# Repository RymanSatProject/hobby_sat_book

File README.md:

# #趣味で作る人工衛星

本リポジトリは、[オーム社 #趣味で作る人工衛星](https://www.ohmsha.co.jp/book/9784274230387/)のサポートページです。

## 構成

### [00_errata](00_errata)

書籍の正誤表が入っています。

### [01_CDH_OBC](01_CDH_OBC)

第7章C&DH系OBCソフトウェアのソースコード

### [02_Mission_OBC](02_Mission_OBC)

第7章ミッションOBCソフトウェアのソースコードおよびセットアップスクリプトが入っています。

### [03_Telecom_OBC](03_Telecom_OBC)

第7章通信OBCソフトウェアのソースコードが入っています。

### [04_Ground_Sta](04_Ground_Sta)

第7章地上局ソフトウェアのインストーラが入っています。

### [05_Schematic](05_Schematic)

第7章EM基板のKiCadファイルが入っています。回路図とCAD画像も入れてあるので、基板作成時にご参照ください。

### [10_Ch7_Sup](10_Ch7_Sup)

第7章の各種補足説明が入っています。

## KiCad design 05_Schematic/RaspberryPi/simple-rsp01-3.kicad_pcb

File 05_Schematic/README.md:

# 回路図面

書籍で作成する基板の回路図を保存しています。使用ソフトウエアはKiCAD (https://www.kicad.org/download/) です。Version6.0以降であれば問題ないと思います。
基板制作時の部品配置や配線の参考にご利用ください。

RaspberryPi RaspberryPiの搭載されている下部基板の図面です。

esp32 Esp32の搭載されている背面基板の図面です。

stm32 STM32の搭載されている上部基板の図面です。

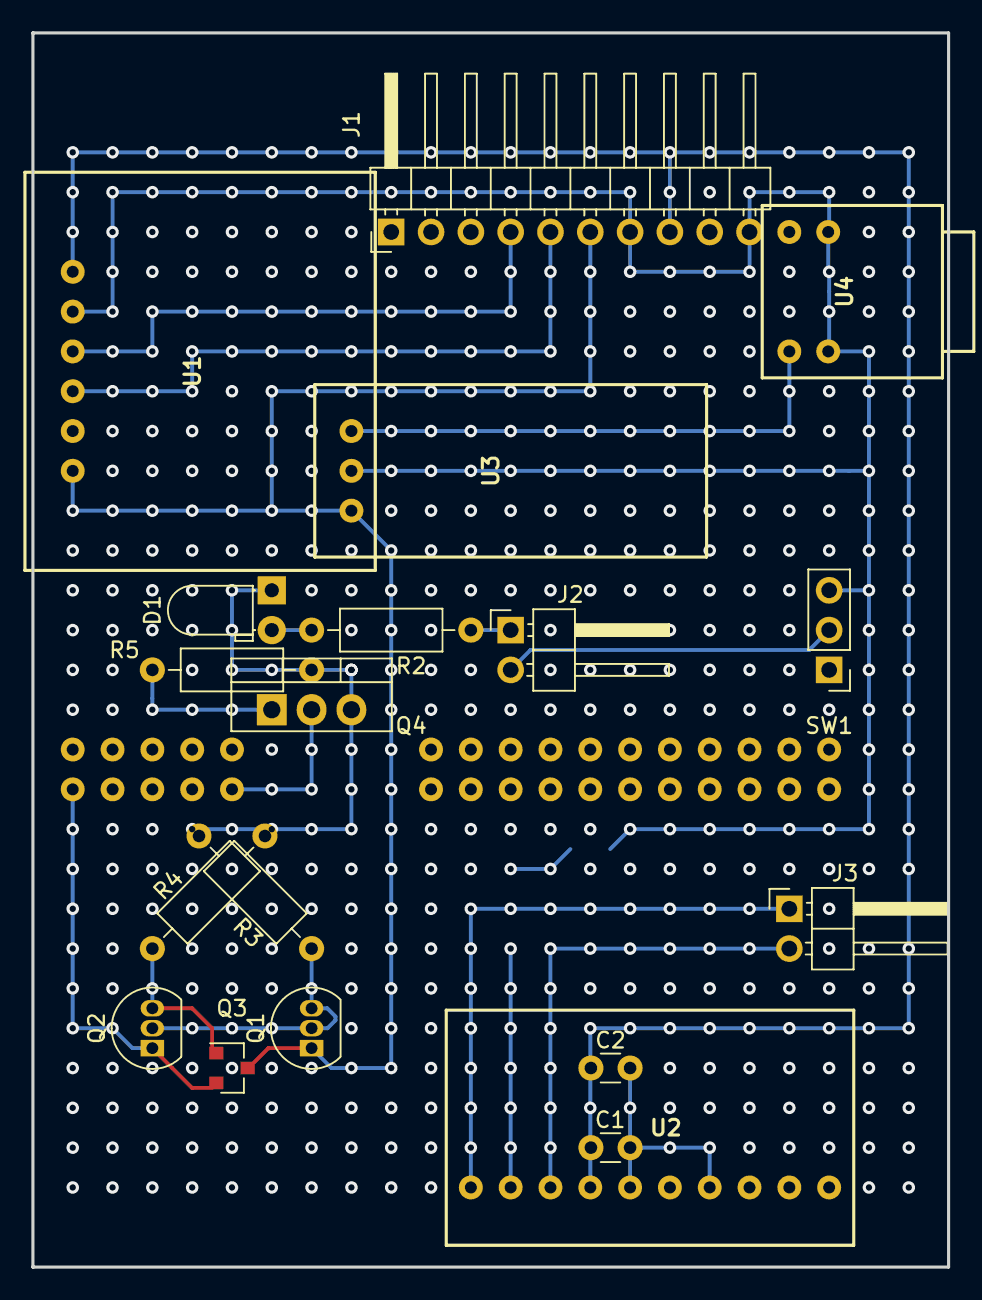
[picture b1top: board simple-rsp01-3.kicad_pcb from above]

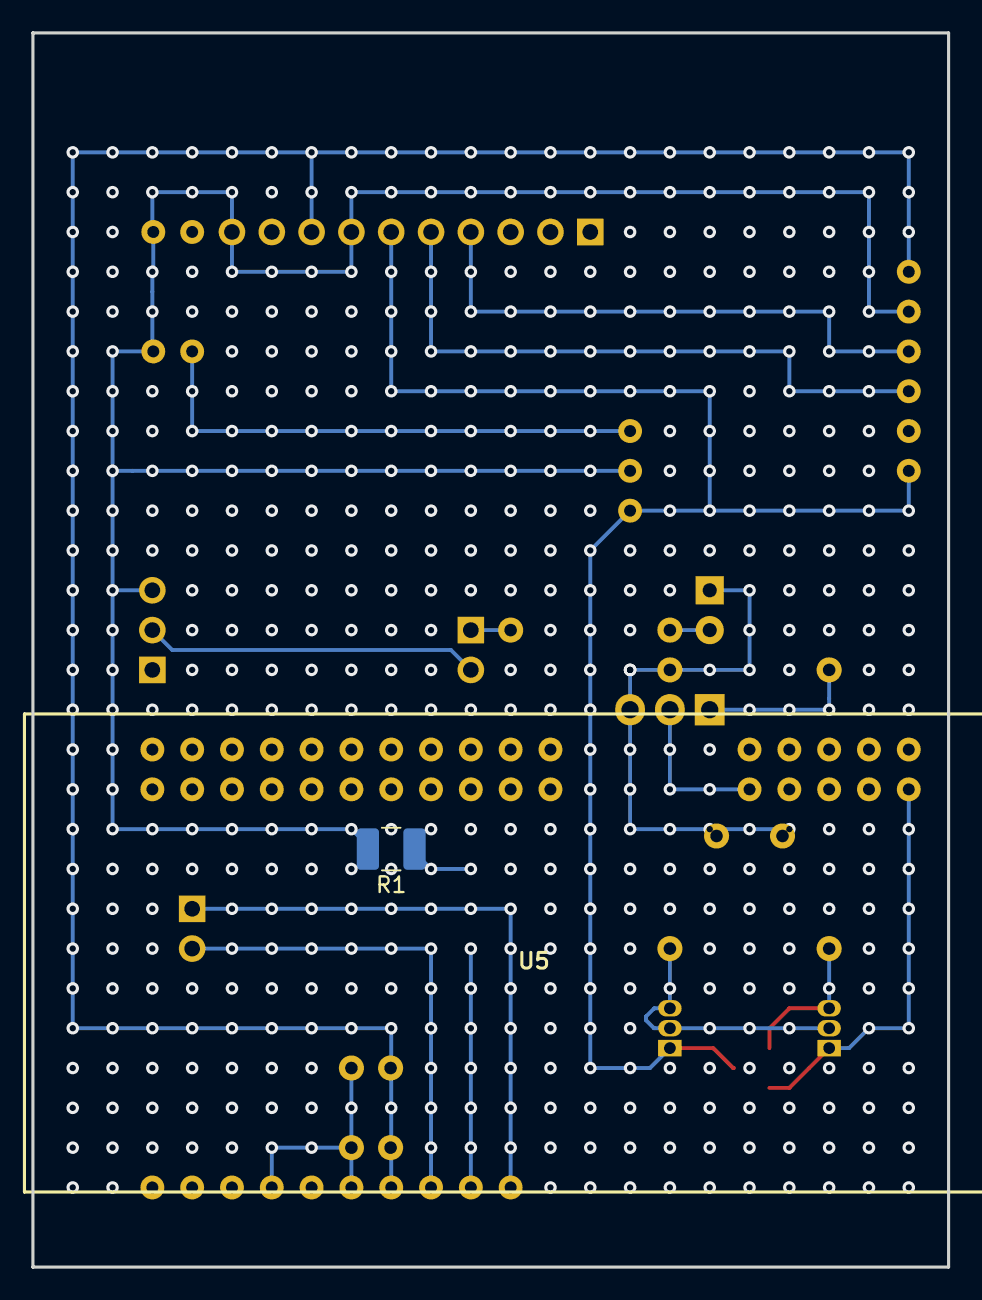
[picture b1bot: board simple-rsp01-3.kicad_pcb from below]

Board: 2 copper layers, 58.4 x 78.7 mm, 21 parts (2 on the bottom side), 19 nets.

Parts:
C1: 0.1uF; C_Disc_D3.0mm_W1.6mm_P2.50mm
C2: 10uF; C_Disc_D3.0mm_W1.6mm_P2.50mm
D1: LED; LED_D3.0mm_Horizontal_O1.27mm_Z2.0mm
J1: Conn_01x10; PinHeader_1x10_P2.54mm_Horizontal
J2, J3: Conn_01x02; PinHeader_1x02_P2.54mm_Horizontal
Q1, Q2: 2N5401L-B-T92-K; TO-92_Inline
Q3: DMG3415U; SOT-23
Q4: MTB30N06I3; TO-220-3_Vertical
R1: 0.24; R_1210_3225Metric_Pad1.42x2.65mm_HandSolder
R2: 330; R_Axial_DIN0207_L6.3mm_D2.5mm_P10.16mm_Horizontal
R3, R4, R5: 10k; R_Axial_DIN0207_L6.3mm_D2.5mm_P10.16mm_Horizontal
SW1: SW_SPDT; PinHeader_1x03_P2.54mm_Vertical
U1: INA219
U2: DRV8830
U3: LXDC55
U4: USBconnector
U5: Raspi; Raspy

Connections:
+3V3: C1.1, C2.1, J1.8, U1.1, U2.4
+4V: J1.6, Q1.1, Q3.3, U1.6, U3.3
+5V: U3.1, U4.1
BAT+: J2.1, R2.1, U1.5
BAT-: J2.2, SW1.2
FROM_Raspi_TX: J1.1, U5.3
GND: C1.2, C2.2, D1.1, J1.7, J1.10, Q4.3, R1.2, R3.2, R4.2, R5.1, SW1.3, U1.2, U2.5, U2.7, U3.2, U4.2, U4.3
MOTOR1: J3.1, U2.1
MOTOR2: J3.2, U2.3
unnamed: D1.2, R2.2
unnamed: Q1.2, Q1.3, Q2.2, R3.1
unnamed: Q2.3, Q3.1, R4.1
unnamed: Q4.2, U5.2
unnamed: R1.1, U2.2
Raspy_3.3V: Q2.1, Q3.2, U5.1
Raspy_Pwrctl: J1.3, Q4.1, R5.2
SCL: J1.4, U1.3, U2.10
SDA: J1.5, U1.4, U2.9
TO_Raspi_RXD: J1.2, U5.4

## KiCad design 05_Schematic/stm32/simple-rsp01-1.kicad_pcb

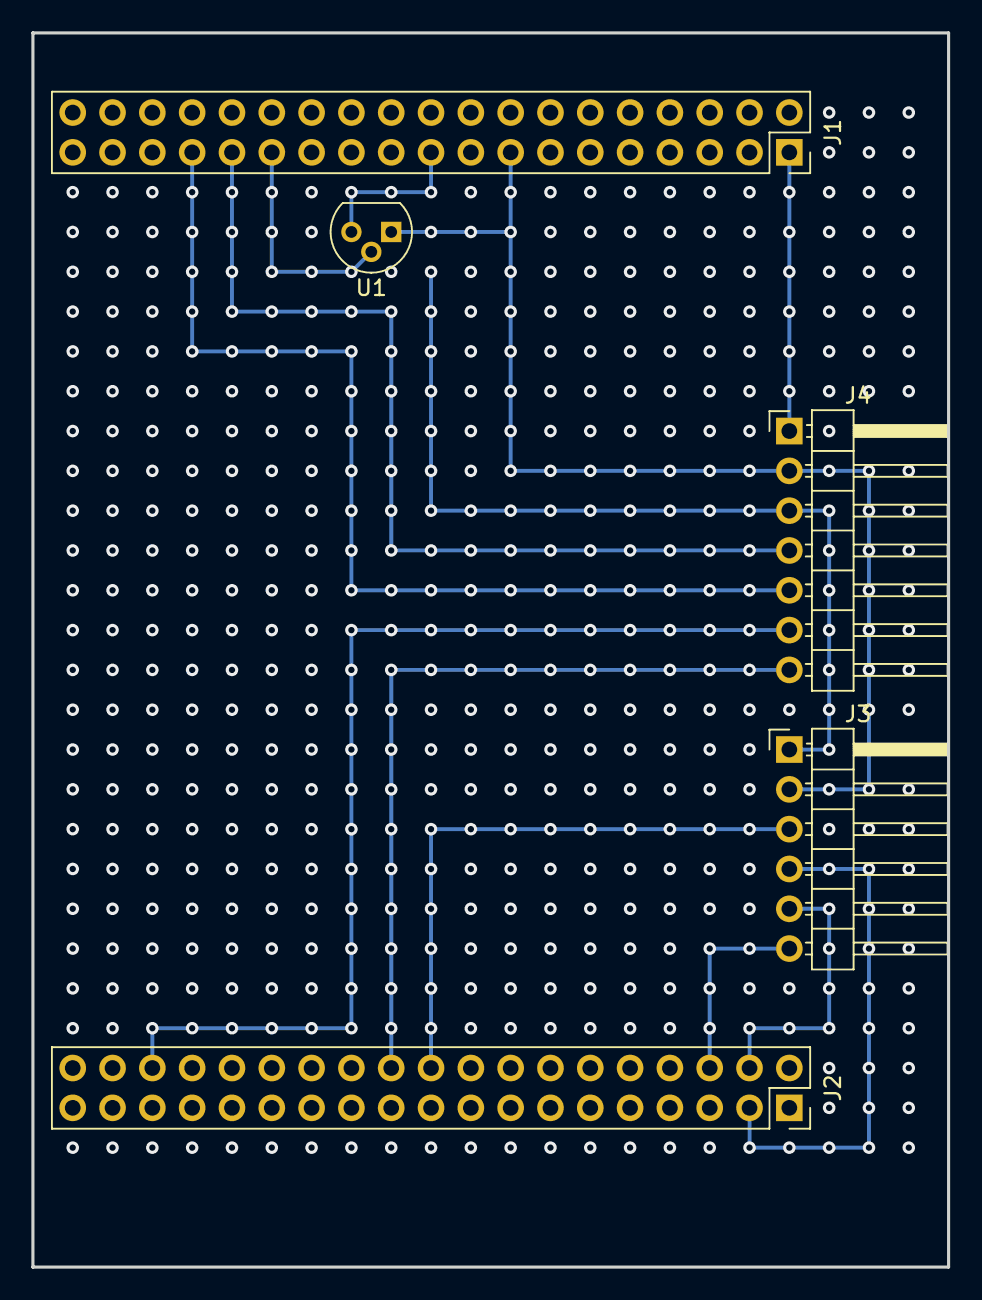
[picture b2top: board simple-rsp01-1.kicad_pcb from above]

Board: 2 copper layers, 58.4 x 78.7 mm, 5 parts (0 on the bottom side), 12 nets.

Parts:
J1, J2: Conn_02x19_Odd_Even; PinSocket_2x19_P2.54mm_Vertical
J3: Conn_01x06; PinHeader_1x06_P2.54mm_Horizontal
J4: Conn_01x07; PinHeader_1x07_P2.54mm_Horizontal
U1: LM61; TO-92

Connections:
+3V3: J1.16, J3.2, J4.2, U1.1
ESP32_GPIO: J1.2, J4.1
FROM_ESP32_TXD: J2.20, J3.3
FROM_Raspi_TX: J2.34, J4.6
GND: J1.20, J3.1, J4.3, U1.3
unnamed: J1.28, U1.2
Raspy_Pwrctl: J1.32, J4.5
SCL: J2.4, J3.5
SDA: J2.6, J3.6
SLIDE_VOL: J1.30, J4.4
TO_ESP32_RXD: J2.3, J3.4
TO_Raspi_RXD: J2.22, J4.7

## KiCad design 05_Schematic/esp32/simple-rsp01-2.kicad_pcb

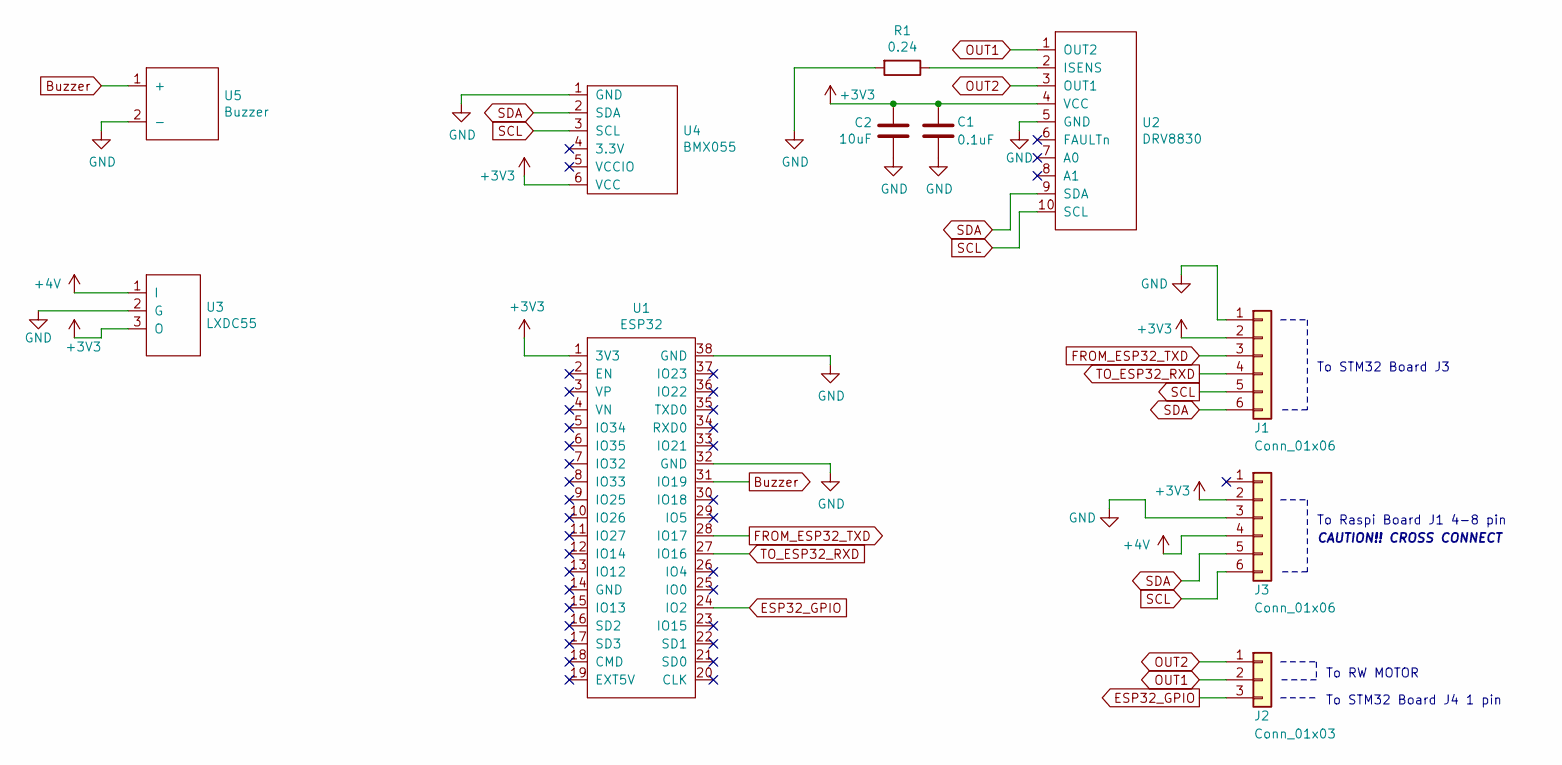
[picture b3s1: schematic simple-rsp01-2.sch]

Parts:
C1: 0.1uF; C_Disc_D3.0mm_W1.6mm_P2.50mm
C2: 10uF; C_Disc_D3.0mm_W1.6mm_P2.50mm
J1, J3: Conn_01x06; PinHeader_1x06_P2.54mm_Horizontal
J2: Conn_01x03; PinHeader_1x03_P2.54mm_Horizontal
R1: 0.24; R_1210_3225Metric_Pad1.42x2.65mm_HandSolder
U1: ESP32
U2: DRV8830
U3: LXDC55
U4: BMX055
U5: Buzzer

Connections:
+3V3: C1.1, C2.1, J1.2, J3.2, U1.1 (3V3), U2.4 (VCC), U3.3 (O), U4.6 (VCC)
+4V: J3.4, U3.1 (I)
Buzzer: U1.31 (IO19), U5.1 (+)
ESP32_GPIO: J2.3, U1.24 (IO2)
FROM_ESP32_TXD: J1.3, U1.28 (IO17)
GND: C1.2, C2.2, J1.1, J3.3, R1.2, U1.32 (GND), U1.38 (GND), U2.5 (GND), U3.2 (G), U4.1 (GND), U5.2 (-)
unnamed: R1.1, U2.2 (ISENS)
OUT1: J2.2, U2.1 (OUT2)
OUT2: J2.1, U2.3 (OUT1)
SCL: J1.5, J3.6, U2.10 (SCL), U4.3 (SCL)
SDA: J1.6, J3.5, U2.9 (SDA), U4.2 (SDA)
TO_ESP32_RXD: J1.4, U1.27 (IO16)

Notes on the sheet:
To STM32 Board J3
To RW MOTOR
To STM32 Board J4 1 pin
To Raspi Board J1 4-8 pin
CAUTION!! CROSS CONNECT

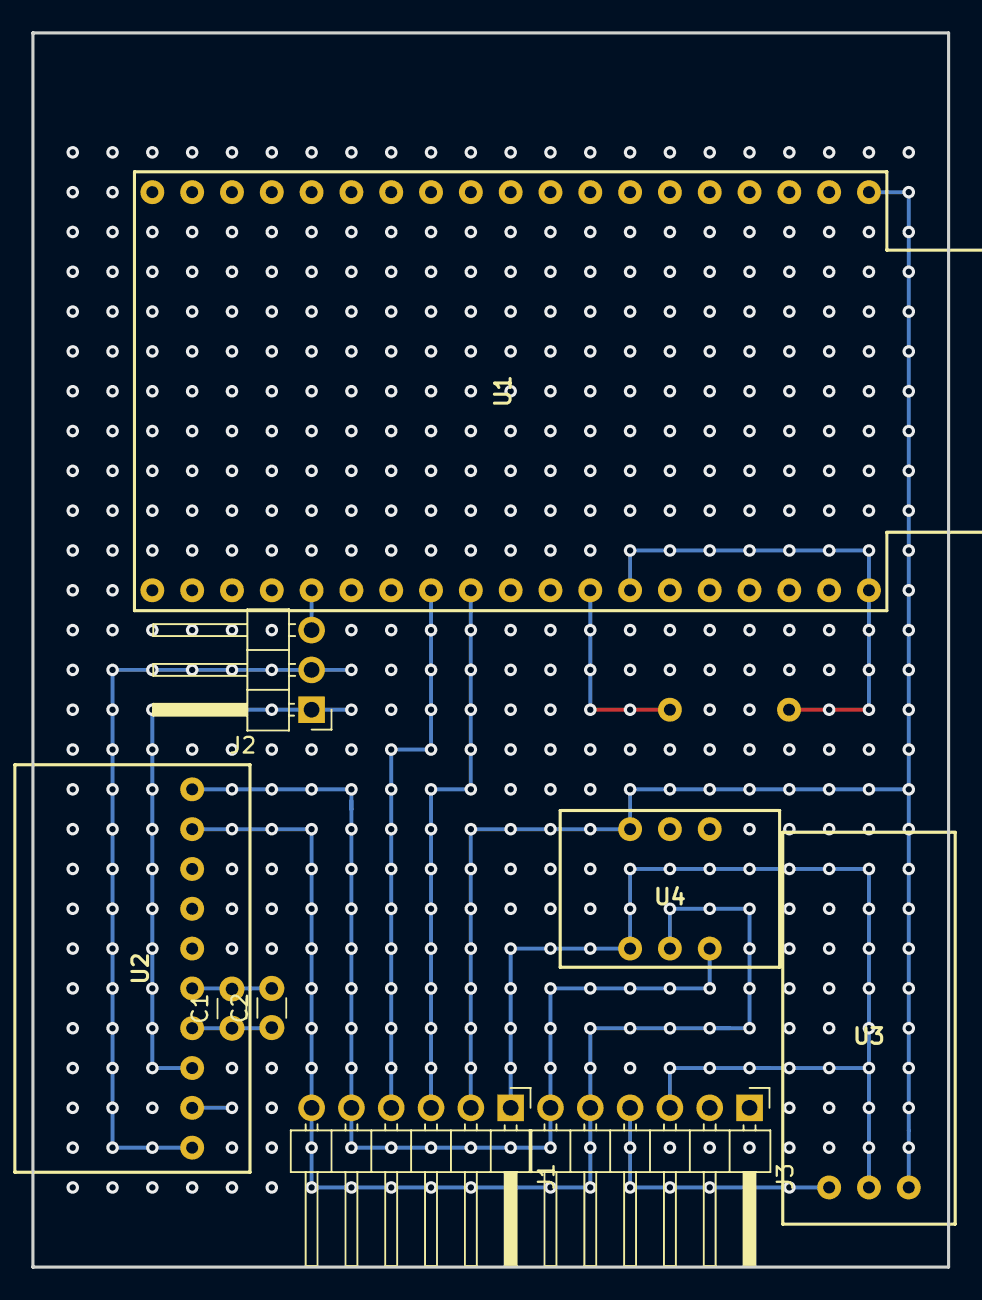
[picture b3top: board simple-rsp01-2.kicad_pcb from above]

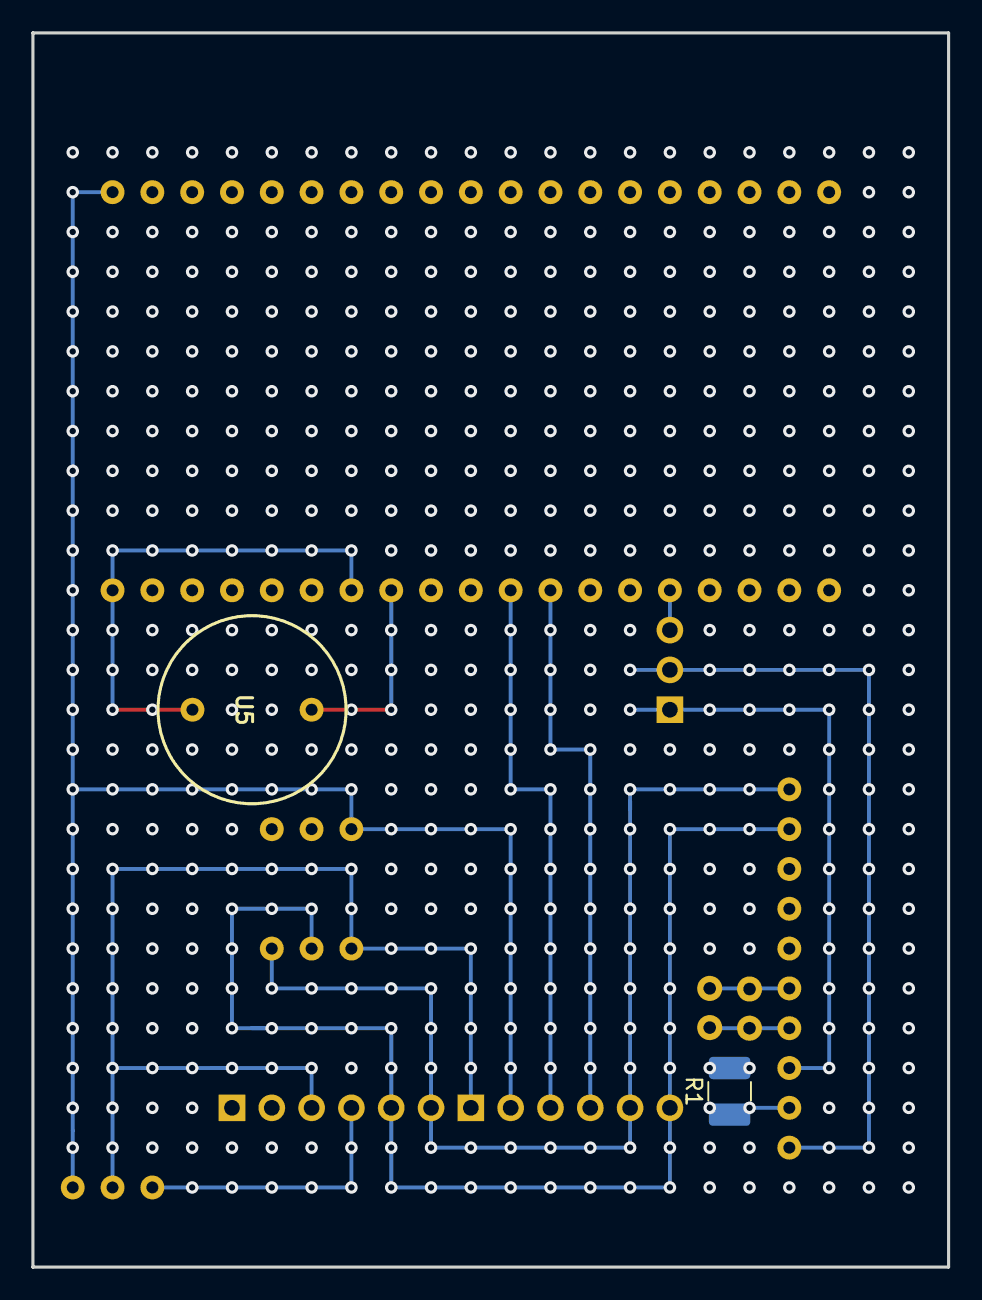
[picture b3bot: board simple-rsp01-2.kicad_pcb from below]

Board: 2 copper layers, 58.4 x 78.7 mm, 11 parts (2 on the bottom side), 12 nets.

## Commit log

2023-01-09 Mission OBC
2023-01-09 Telecomunication OBC
2023-01-09 地上局ソフト
2023-01-09 7章 簡易RSP-01を作ってみよう補足説明
2023-01-09 各基板図面
2023-04-15 mission init base
2023-04-15 mission init
2023-04-15 grand init
2023-04-15 mission log dir
2023-04-15 schematic init
2023-04-15 telecom init
2023-04-15 readme
2023-04-15 errata: LED、zipダウンロード方法
2023-04-15 10_Ch7_Sup init
2023-04-15 init
2023-04-21 lfs off
2023-04-21 zipの軽量化
2023-04-21 zip軽量化
2023-04-21 update errata
2023-04-29 Raspberry Piの設定補足を追加
2023-04-29 DD For Windowsのダウンロード方法を追記
2023-04-29 セットアップ開始のプロンプト確認を追加
2023-05-06 正誤表追加
2023-05-06 回路データ更新
2023-05-06 デバッグコマンドの修正
2023-05-06 パーツリスト更新
2023-05-06 アームに関する説明の追加
2023-05-06 重複ファイルの削除
2023-05-13 メインOBCの文字入出力の説明の追加
2023-05-16 type
2023-05-16 M系基板の回路図の更新
2023-05-21 初版での修正画像
2023-05-21 正誤表の更新
2023-05-21 Ubuntu 20.04.6 LTSの注釈を追加
2023-05-23 P.144 図9でBMX055表示が出ない場合
2023-05-27 正誤表 P.161 追加
2023-06-04 Mission基板FET配線誤りの修正
2023-06-04 P168 図51 Q4の配線誤りの修正
2023-06-04 代替購入先の追記
2023-08-25 コマンドリストを追加
2023-09-16 エラッタ追加（P147 power_mwの式の修正）
2023-10-08 aptリポジトリの変更
